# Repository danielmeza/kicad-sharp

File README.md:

# KiCadSharp

A .NET client for [KiCad](https://www.kicad.org/). Drive a running pcbnew over KiCad's IPC API, and
read and write symbol libraries, footprints, boards and schematics off disk.

```
dotnet add package KiCadSharp
```

```csharp
using KiCadSharp;
using Microsoft.Extensions.DependencyInjection;

var services = new ServiceCollection();
services.AddLogging();
services.AddKiCad("my-plugin");

var kicad = services.BuildServiceProvider()
                    .GetRequiredService<IKiCadFactory>()
                    .Create("my-plugin");

var board = await kicad.GetBoard();
var footprints = await board.GetItems(KiCadObjectType.KotPcbFootprint);

Console.WriteLine($"{footprints.Count} footprints on {board.Name}");
```

KiCad has to be running with **Preferences → Plugins → Enable IPC API** ticked. No token needed —
the client picks one up on the first round trip.

## Before you start

**This works against `pcbnew`. It does not work against `eeschema` on KiCad 10.0.6** — that build
registers essentially nothing over IPC, not even `GetVersion`. The schematic commands land in
KiCad 11. What we measured is in [docs/ipc.md](docs/ipc.md).

Against KiCad master (`10.99.0`, the 11.0 line) `eeschema` does answer, and `kicad.GetSchematic()`
wraps it, along with the embedded-file, variant, library, job and cross-probe commands master added.
`KiCadVersion.SupportsSchematic` and its sibling flags say which KiCad you are talking to. All of
it is measured live against a master nightly in CI (`KICADSHARP_KICAD_FLAVOR=nightly` with the
test harness); see [docs/ipc.md](docs/ipc.md) for what master handles and what it only declares.

**On disk, the typed document model is a set of views**: `KiCadSymbolLibrary`, `KiCadFootprintLibrary`,
`KiCadBoard` and `KiCadSchematic` read and write the file's own s-expressions, and an untouched save
is byte-identical. Not every form has a view yet, and the write path is partial;
[docs/status.md](docs/status.md) says exactly where. Anything without a view is still reachable,
losslessly, through `Node`, [SExpressions](https://github.com/danielmeza/sexpressions) or the
`kicadsharp` CLI below.

## The packages

| Package | What it's for |
|---|---|
| [`KiCadSharp`](https://www.nuget.org/packages/KiCadSharp) | The client: IPC, plus the on-disk symbol, footprint, board and schematic formats, copper geometry checked against KiCad's own, and Specctra DSN export and session import for an autorouter. |
| [`KiCadSharp.Fluent`](https://www.nuget.org/packages/KiCadSharp.Fluent) | A fluent style for building documents: a chainable `With*` for every `Add*`. Optional, and layered over `KiCadSharp` — see [below](#two-ways-to-build-a-document). |
| [`KiCadSharp.Protos`](https://www.nuget.org/packages/KiCadSharp.Protos) | Generated C# types for KiCad's protobuf API. Separate package because they appear in `KiCadSharp`'s public surface. |
| [`KiCadSharp.Cli`](https://www.nuget.org/packages/KiCadSharp.Cli) | A dotnet tool, `kicadsharp`, for s-expression files from a shell. |

## The CLI

```
dotnet tool install --global KiCadSharp.Cli
```

```
kicadsharp parse    <file>                 forms, nodes, depth
kicadsharp fmt      <file> [--in-place]    reformat through a verified round trip
kicadsharp query    <file> <path> [--all]  read a value by path
kicadsharp validate <file>                 does it parse? non-zero if not
```

```
$ kicadsharp query board.kicad_pcb kicad_pcb/general/thickness
1.6
```

`fmt` re-parses its own output and compares the trees before writing anything, so a clean run is the
proof the round trip was lossless. It refuses `--in-place` when it would drop content.

## Two ways to build a document

`KiCadSharp` builds a document with `Add*` methods. Each returns the child it created, so you keep a
handle on it:

```csharp
using KiCadSharp.Documents;

string[] smd = ["F.Cu", "F.Paste", "F.Mask"];

var footprint = new KiCadFootprint("R_0603_1608Metric");
footprint.AddPad("1", "smd", "rect", -0.8, 0, 0.9, 0.95, smd);
footprint.AddPad("2", "smd", "rect", 0.8, 0, 0.9, 0.95, smd);
footprint.AddLine(-1.5, -0.7, 1.5, -0.7, "F.CrtYd", 0.05);
var model = footprint.AddModel("${KICAD10_3DMODEL_DIR}/Resistor_SMD.3dshapes/R_0603_1608Metric.step");
model.Scale = new KiCadXyz(1, 1, 1);
```

`KiCadSharp.Fluent` adds a `With*` for each of them. It returns the parent, so the calls chain, and
takes an optional callback that receives the child, so chaining never costs you the handle:

```
dotnet add package KiCadSharp.Fluent
```

```csharp
using KiCadSharp.Documents;
using KiCadSharp.Fluent;

string[] smd = ["F.Cu", "F.Paste", "F.Mask"];

var footprint = new KiCadFootprint("R_0603_1608Metric")
    .WithPad("1", "smd", "rect", -0.8, 0, 0.9, 0.95, smd)
    .WithPad("2", "smd", "rect", 0.8, 0, 0.9, 0.95, smd)
    .WithLine(-1.5, -0.7, 1.5, -0.7, "F.CrtYd", 0.05)
    .WithModel("${KICAD10_3DMODEL_DIR}/Resistor_SMD.3dshapes/R_0603_1608Metric.step",
               model => model.Scale = new KiCadXyz(1, 1, 1));
```

Both build the same footprint and save the same bytes; the package's tests hold it to that. Neither
style replaces the other. The `Add*` API is unchanged, both work on the same objects, and you can
mix them. Items that are added through a live list rather than an `Add*` get a `With` too:
`board.Zones.With(zone => zone.WithPoint(0, 0).WithPoint(10, 0).WithPoint(10, 10))`. The full list is
in [docs/api.md](docs/api.md#kicadsharpfluent).

## More examples

**Edit the board inside a commit**

```csharp
var board = await kicad.GetBoard();
var commit = await board.BeginCommit();

// ... change items ...

await board.PushCommit(commit, "move the connector");
```

**Read a symbol library from disk**

```csharp
var lib = KiCadSymbolLibrary.Load("orbion.kicad_sym");

foreach (var symbol in lib.Symbols)
    Console.WriteLine($"{symbol.Id}: {symbol.Pins.Count} pins");

lib.Save("orbion.kicad_sym");
```

**Net classes and text variables**

```csharp
var board = await kicad.GetBoard();
var classes = await board.GetProject().GetNetClasses();
var expanded = await board.ExpandTextVariables("${ORBION_PN} rev ${BOARD_REV}");
```

Expand through the document rather than the project: the board's resolver sees the project's
variables too, and on KiCad 10.0.6 pcbnew rejects a project-scoped expansion before KiCad's own
project handler can answer it (measured; docs/ipc.md).

Every type and member: [docs/api.md](docs/api.md).

## Platforms

`net10.0`. The transport talks to [nng](https://nng.nanomsg.org/) through P/Invoke, and the native
library ships in the package for eight runtime identifiers:

| | x64 | arm64 | 32-bit |
|---|---|---|---|
| Linux (glibc) | `linux-x64` | `linux-arm64` | `linux-arm` |
| macOS | `osx-x64` | `osx-arm64` (Apple silicon) | — |
| Windows | `win-x64` | `win-arm64` | `win-x86` |

Anything else, musl (Alpine) included, gets no `libnng` from the package: point
`KICADSHARP_NNG_LIBRARY` at one you supply. What each library links against, and where that bites (a
slim container, the Visual C++ runtime on Windows), is in
[docs/ipc.md](docs/ipc.md#nng-and-which-platforms-it-reaches).

## Building

```
git clone https://github.com/danielmeza/kicad-sharp
cd kicad-sharp
dotnet test
```

KiCad's `.proto` files are vendored under `protos/`, pinned to one KiCad commit — no submodule, no
1.4 GB checkout. To build against a local SExpressions checkout, or to run the tests against a real
`kicad-cli` or keep the files they write, see [docs/building.md](docs/building.md).

## Contributing

Issues and pull requests welcome. If you're reporting something about IPC, say which KiCad version
and which editor: pcbnew and eeschema behave very differently.

## License

MIT — see [LICENSE](LICENSE).

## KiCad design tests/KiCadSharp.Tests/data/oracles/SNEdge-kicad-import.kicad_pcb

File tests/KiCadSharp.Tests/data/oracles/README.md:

# Oracles: what KiCad itself answers

Every file here was written by **pcbnew 10.0.6** — the `pcbnew` Python module inside
`localhost/orbion/kicad-release:10.0.6`, host version `10.0.6-10.0.6~ubuntu26.04.1` — or, for the
one session, by **Freerouting 2.4.1** from a design pcbnew wrote. They are the other side of the
comparisons in `Geometry/` and `Specctra/`: this library's answer is asserted against KiCad's, never
against its own.

The scripts that produced them are not committed: they are three to ten calls into `pcbnew`, which is
Python-only, and this repository ships none. What they called is recorded here instead, so an oracle
can be regenerated and a changed number traced to a changed KiCad.

| File | Produced by | From |
|---|---|---|
| `SNEdge.dsn`, `bitaxeGamma.dsn`, `m2-pcie-adapter.dsn` | `pcbnew.ExportSpecctraDSN(pcbnew.LoadBoard(board), path)` | the vendored boards in `../snedge/`, `../bitaxe-gamma/`, `../antmicro-m2-pcie-adapter/`, with no project file beside them, so KiCad's own default net class |
| `SNEdge-unrouted.kicad_pcb` | `LoadBoard(SNEdge)`; every track, arc and via `board.Remove`d except the `VCC` net's, which were `SetLocked(True)`; `SaveBoard` | `../snedge/SNEdge.kicad_pcb` |
| `SNEdge-unrouted.dsn` | `ExportSpecctraDSN` of the board above | — |
| `SNEdge-unrouted.ses` | `java -jar freerouting-2.4.1.jar --gui.enabled=false -de SNEdge-unrouted.dsn -do SNEdge-unrouted.ses -mp 6 -mt 8 --router.automatic_neckdown=false --router.plane_nets=GND` in `eclipse-temurin:25-jre`; the jar is SHA-256 `251101c3…afc6aa9` | the design above |
| `SNEdge-kicad-import.kicad_pcb` | `pcbnew.ImportSpecctraSES(LoadBoard(SNEdge-unrouted), SNEdge-unrouted.ses)`; `SaveBoard` — 71 tracks, 13 of them the locked ones kept, 8 vias | the board and session above |
| `pad-shapes.kicad_pcb` | `pcbnew.NewBoard`, then 36 footprints of one pad each — trapezoid, chamfered, chamfered with rounding, custom (a filled polygon and a stroked one), oval and rectangle offset from their holes — at 0°, 30° and 90°, on both sides, each ringed by eight 0.2 mm tracks and a via | — |
| `pad-shapes.dsn` | `ExportSpecctraDSN` of the board above | — |
| `*.distances.json` | for every pair of copper items on a shared copper layer whose boxes come within 1 mm: `a.GetEffectiveShape(layer).Collide(b.GetEffectiveShape(layer), clearance)` bisected on `clearance` to 0.1 µm. Up to 2,000 / 3,000 / 5,000 pairs, shuffled with seed 7 | `SNEdge`, `bitaxeGamma`, `pad-shapes` |
| `custom-primitives.kicad_pcb` | in `ghcr.io/danielmeza/orbion-kicad-release:10.0.6`, same host version: `pcbnew.CreateEmptyBoard`, then `pcbnew.FootprintLoad` of twelve hand-written footprints of one custom pad each, whose primitives are the forms 10.0.6 writes — four Béziers (an arch, an S, a loop, a hairpin), a rounded rectangle filled, filled with a pen, stroked, with a radius past half its shorter side, and stroked into a circle, an arc, filled and stroked circles, a stroked rectangle and a line — at 0°, 30° and 90° on both sides (`Rotate`, then `Flip` left-right), each ringed by 0.2 mm vias and 0.1 mm tracks placed 0.02 to 0.18 mm off a primitive's edge along its normal, on both sides of a stroke; `SaveBoard` | — |
| `custom-primitives.dsn` | `ExportSpecctraDSN` of the board above | — |
| `custom-primitives.distances.json` | every custom pad against every via and track whose box comes within 1 mm of it: the same `Collide`, bisected to 1 nm. 1,830 pairs | `custom-primitives` |
| `outline-curves.kicad_pcb` | in `ghcr.io/danielmeza/orbion-kicad-release:10.0.6`, same host version: `pcbnew.CreateEmptyBoard`, then on `Edge.Cuts` three `PCB_SHAPE` segments closed by a Bézier (`SetBezierC1`, `SetBezierC2`), a rectangle inside them with `SetCornerRadius` past half its shorter side, a rounded rectangle of its own, and `pcbnew.FootprintLoad` of four hand-written footprints — a lone pad, twice, on one net and joined by a `PCB_TRACK`; an `fp_rect (radius 2)` around a pad, at 30° and again at 90°; an `fp_line` closed by an `fp_curve` around a pad at −30°; two `fp_curve`s closing a pillow at 45°, inside the first outline; `SaveBoard` | — |
| `outline-curves.dsn` | `ExportSpecctraDSN` of the board above | — |

What KiCad itself does that the tests had to learn, all measured on these files:

- **KiCad reads an arc, and a chamfered pad's rounded corner, up to 5 µm too far away.** Its
  effective shape for both is a polygon at `ARC_HIGH_DEF` / the pad's `GetMaxError()` of 5 µm with
  `ERROR_INSIDE`. `CopperGeometryOracleTests` says how that was established.
- **KiCad 10 writes a chamfered pad as `roundrect`**, with `(chamfer_ratio …)` and `(chamfer …)`
  beside it. `chamfered_rect` appears nowhere in `pad-shapes.kicad_pcb`, which holds twelve chamfered
  pads.
- **`Padstack().AddPrimitive(PCB_SHAPE, layer)` segfaults `SaveBoard` in 10.0.6.** The stroked
  primitive on the custom pads was added with `AddPrimitivePoly(layer, polygon, width, filled=False)`
  instead.
- **KiCad cuts a Bézier into chords within its max error**, 5 µm by default (`BEZIER_POLY::GetPoly`),
  for DRC as for plotting. The chords cut the inside of each bend, so KiCad reads a neighbour inside a
  bend up to 5 µm too close and one outside it up to 5 µm too far. `CopperGeometryOracleTests` says
  how that was established.
- **KiCad writes a custom pad to a design as a convex hull**, of the polygon
  `PAD::MergePrimitivesAsPolygon` draws (`EXPORT_CUSTOM_PADS_CONVEX_HULL`, `specctra_export.cpp`).
  All 3 custom padstacks in `pad-shapes.dsn` and all 35 in `custom-primitives.dsn` are convex, to
  within 4 nm.
- **KiCad 10.0.6 collides a track with a full circle as if the circle had no pen.** A stroked
  `gr_circle`, a filled one with a pen, and a rounded rectangle that is a circle all become a
  360° `SHAPE_ARC`, and `SHAPE_ARC::Collide(const SEG&)` takes a full-circle branch that never adds
  the arc's width (`shape_arc.cpp` L301-313). Measured: tracks read 50 or 75 µm too far — half the
  pen — and a track inside a ring was not seen at all, while vias read right. So the pads in
  `custom-primitives.kicad_pcb` that hold a full circle are ringed by vias only.
- **KiCad 10.0.6 draws a stroked rectangle whose corner radius makes it a circle as a dot** the width
  of the pen. `ROUNDRECT::TransformToPolygon` makes its outline one 360° arc, and
  `TransformArcToPolygon` finds no chord between its equal ends (`ARC_CHORD_PARAMS::Compute`) and
  draws a pen stroke from the start to the start. `MergePrimitivesAsPolygon` returns that dot, the
  design's hull is of it, and a Gerber of `F.Cu` plotted by `kicad-cli` 10.0.6 flashes it; its DRC
  shape is the whole ring.
- **KiCad clamps a rectangle's corner radius to half its shorter side** as it loads it
  (`EDA_SHAPE::SetCornerRadius`), and writes the clamped value back.
- **KiCad draws a Bézier on `Edge.Cuts` within the board's max error**, 5 µm by default, with
  vertices on the curve and chords cutting the inside of each bend
  (`RebuildBezierToSegmentsPointsList(aErrorMax)`, `convert_shape_list_to_polygon.cpp`). Measured
  on `outline-curves.dsn`, whose boundary is `BOARD::GetBoardPolygonOutlines`: 71 vertices on the S
  curve, and the curve sags at most 4.98 µm from them.
- **KiCad draws a rectangle's corner radius on `Edge.Cuts`** (`ROUNDRECT::TransformToPolygon` at
  the shape's max error, same file), with vertices *outside* the true arc: 0 to 0.99 µm on the
  108 vertices of the `fp_rect` of radius 2, 0 to 0.55 µm on the 164 of the `gr_rect` of radius 5
  and on the 126 of the stadium hole of radius 3. That hole's box runs 9.9995 to 22.0005 for a
  rectangle drawn 10 to 22. The arcs of the polygon it made of the rectangle it turned by 30° come
  out −0.05 to 0.55 µm from the arc they were.
- **pcbnew saves a rectangle inside a footprint placed off-axis as a polygon.** A rectangle is
  axis-aligned by definition, so turning the footprint by 30° turned `RR1`'s `fp_rect (radius 2)`
  into an `fp_poly` whose `pts` are four `(arc (start …) (mid …) (end …))` entries and nothing
  else, the straight sides implied between them; the same footprint at 90°, `RR2`, kept its
  `fp_rect` and its `(radius 2)`. Measured in `outline-curves.kicad_pcb`.
- **KiCad's design export infers an outline when none closes.** `SPECCTRA_DB::BuiltBoardOutlines`
  calls `GetBoardPolygonOutlines(…, aInferOutlineIfNecessary = true)`, which falls back to the box
  around `Edge.Cuts`, then around everything (`specctra_export.cpp` L240,
  `BuildBoardPolygonOutlines`). This library refuses such a board instead. Read in the source, not
  measured: every outline here closes.
- **KiCad writes a footprint's `fp_line` on `Edge.Cuts` into its image as an `outline`, and not
  its `fp_curve`.** Measured on `outline-curves.dsn`: image `DEE` carries
  `(outline (path signal 100 -5000 5000 -5000 -5000))` for its line and nothing for its curve;
  `PILLOW`, two curves, carries none. The tests compare no image outline.

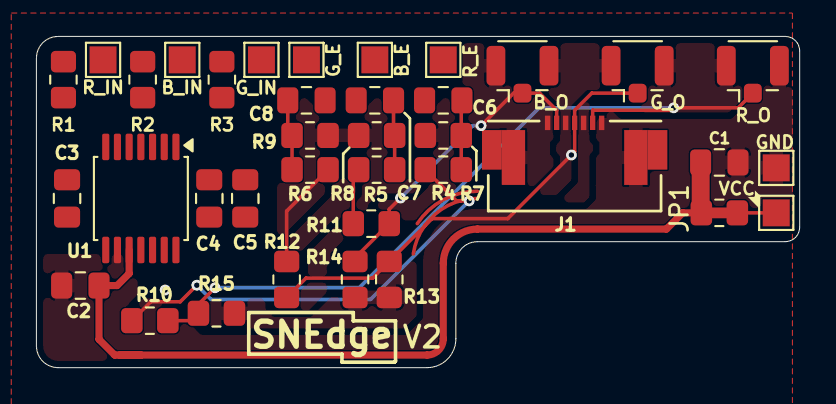
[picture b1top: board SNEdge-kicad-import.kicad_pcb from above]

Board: 2 copper layers, 42.4 x 18.4 mm, 37 parts (0 on the bottom side), 18 nets.

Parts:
C1: 22uF; C_0805_2012Metric_Pad1.18x1.45mm_HandSolder
C2, C6, C7, C8: 1uF; C_0805_2012Metric_Pad1.18x1.45mm_HandSolder
C3, C4, C5: 10pF; C_0805_2012Metric_Pad1.18x1.45mm_HandSolder
J1: RGB_OUT; CON_527460771_MOL
J8: G_O; U.FL_Hirose_U.FL-R-SMT-1_Vertical
J9: B_O; U.FL_Hirose_U.FL-R-SMT-1_Vertical
J10: R_O; U.FL_Hirose_U.FL-R-SMT-1_Vertical
JP1: INPUT JUMPER; R_0805_2012Metric_Pad1.20x1.40mm_HandSolder_Jumper_Closed
R1, R2, R3: 7.5k; R_0805_2012Metric_Pad1.20x1.40mm_HandSolder
R4, R5, R6: 430R; R_0805_2012Metric_Pad1.20x1.40mm_HandSolder
R7, R8, R9: 75R; R_0805_2012Metric_Pad1.20x1.40mm_HandSolder
R10, R11, R12: 240R; R_0805_2012Metric_Pad1.20x1.40mm_HandSolder
R13, R14, R15: 110R; R_0805_2012Metric_Pad1.20x1.40mm_HandSolder
TP1: VCC; TestPoint_Pad_1.5x1.5mm
TP2: GND; TestPoint_Pad_1.5x1.5mm
TP3: G_IN; TestPoint_Pad_1.5x1.5mm
TP4: B_IN; TestPoint_Pad_1.5x1.5mm
TP5: R_IN; TestPoint_Pad_1.5x1.5mm
TP6: R_E; TestPoint_Pad_1.5x1.5mm
TP7: B_E; TestPoint_Pad_1.5x1.5mm
TP8: G_E; TestPoint_Pad_1.5x1.5mm
U1: THS7376; TSSOP-14_4.4x5mm_P0.65mm

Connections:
GND: C1.1, C2.1, J1.1, J1.3, J1.5, J1.7, J1.MP (MountPin), J8.2 (Ext), J9.2 (Ext), J10.2 (Ext), R1.1, R2.1, R3.1, R7.2, R8.2, R9.2, R13.2, R14.2, R15.2, TP2.1 (1_1), U1.1 (CH1_IN), U1.5 (GND), U1.6 (DISABLE), U1.9 (BYPASS)
unnamed: C6.1, R4.2, R7.1
unnamed: C6.2, TP6.1 (1_1)
unnamed: C7.1, R5.2, R8.1
unnamed: C7.2, TP7.1 (1_1)
unnamed: C8.1, R6.2, R9.1
unnamed: C8.2, TP8.1 (1_1)
unnamed: J1.2, J9.1 (In), R11.1, R14.1
unnamed: J1.4, J8.1 (In), R12.1, R13.1
unnamed: J1.6, J10.1 (In), R10.1, R15.1
unnamed: JP1.1 (A), TP1.1 (1_1)
unnamed: C5.2, R3.2, TP3.1 (1_1), U1.2 (CH2_IN)
unnamed: C5.1, R6.1, R12.2, U1.13 (CH2_OUT)
unnamed: C4.2, R2.2, TP4.1 (1_1), U1.3 (CH3_IN)
unnamed: C4.1, R5.1, R11.2, U1.12 (CH3_OUT)
unnamed: C3.2, R1.2, TP5.1 (1_1), U1.4 (CH4_IN)
unnamed: C3.1, R4.1, R10.2, U1.11 (CH4_OUT)
VCC: C1.2, C2.2, JP1.2 (B), U1.10 (V_{S+})

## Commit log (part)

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2025-05-09 Update solution and fix several kicad proto issues
2025-05-10 Update: - Avalonia to 11.3.0 - Avalonia.Desktop to 11.3.0 - Avalonia.Diagnostics to 11.3.0 - Avalonia.Fonts.Inter to 11.3.0 - Avalonia.Themes.Fluent to 11.3.0 - Avalonia.Xaml.Interactions to 11.3.0 -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
    ---
    updated-dependencies:
    - dependency-name: Avalonia
    dependency-version: 11.3.0
    dependency-type: direct:production
    update-type: version-update:semver-minor
